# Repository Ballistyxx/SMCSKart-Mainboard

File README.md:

# SMCSKart Mainboard

Custom PCB integrating every system in the SMCS Robotics 8th period go-kart. The board acts as the central hub between a Raspberry Pi 4, a Teensy 4.1, all motor controller I/O, sensors, and peripherals.

<div style="display: flex; justify-content: space-between;">

</div>

---

## Components

| Component | Description |
|-----------|-------------|
| Raspberry Pi 4 | Main compute; connected via 40-pin header |
| Teensy 4.1 | Real-time microcontroller with onboard Ethernet |
| NEO-M9N | GPS module (connected to Pi I2C + PPS to Teensy) |
| MPU6050 | 6-axis accelerometer/gyroscope (connected to Pi I2C) |
| MCP4725 | 12-bit DAC for throttle signal generation (connected to Teensy I2C) |
| MCP2562-E/P | CAN bus transceiver |
| IRLZ44N | Logic-level N-channel MOSFETs for all toggle/switch outputs (with pulldown resistors) |
| ND721000 | FarDriver BLDC/PMSM speed controller (RS232 interface) |

---

## Power Rails

The board supplies three voltage rails available on the extra power port:

| Rail | Voltage |
|------|---------|
| 3V3 | 3.3 V |
| 5V | 5 V |
| 24V | 24 V (also used for LED strip) |

---

## Teensy 4.1 Pin Assignments

### Serial / UART

| Pin(s) | Interface | Connected To | Notes |
|--------|-----------|--------------|-------|
| 0, 1 | Serial1 (TX, RX) | ND721000 ESC | RS232 level — programming/telemetry port on ESC |
| 7, 8 | Serial2 (TX, RX) | Raspberry Pi 4 | UART bridge between Teensy and Pi |
| 14, 15 | Serial3 (TX, RX) | Transceiver module | RF/wireless transceiver comms |
| 34, 35 | Serial8 (TX, RX) | FPV camera | UART control for FPV camera |

### I2C

| Pin(s) | Bus | Connected To |
|--------|-----|--------------|
| 18, 19 | SDA, SCL | MCP4725 DAC (throttle control) |

### CAN Bus

| Pin(s) | Signal | Notes |
|--------|--------|-------|
| 30, 31 | CRX, CTX | Via MCP2562-E/P transceiver; 120 Ω termination required at each end |

### Digital I/O — ESC Control & Sensors

All toggle output pins drive an IRLZ44N MOSFET with a pulldown resistor, providing an active-low ground signal to the ESC connector.

| Pin | Function | ESC Signal | Direction |
|-----|----------|------------|-----------|
| 2 | Hall Pulses input | Hall Pulses (ESC pin 18) | Input from ESC |
| 3 | Reverse toggle | REV (ESC pin 8) | Output to ESC |
| 4 | Brake toggle | Low Brake (ESC pin 21) | Output to ESC |
| 5 | High speed toggle | High Speed (ESC pin 3) | Output to ESC |
| 6 | Low speed toggle | Low Speed (ESC pin 2) | Output to ESC |
| 9 | Cruise control | Cruise/Boost connector | Output to ESC |
| 10 | PPS | NEO-M9N GPS pulse-per-second | Input from GPS |
| 32 | Contactor toggle | Main contactor relay | Output |

### PWM — LED Strip (24 V)

| Pin | Channel |
|-----|---------|
| 37 | Red |
| 36 | Green |
| 33 | Blue |

### Auxiliary (EX1–EX5)

| Pin | Label |
|-----|-------|
| 25 | EX1 |
| 26 | EX2 |
| 27 | EX3 |
| 28 | EX4 |
| 29 | EX5 |

---

## Raspberry Pi 4 I2C Bus

| Device | Address | Function |
|--------|---------|----------|
| NEO-M9N | — | GPS module |
| MPU6050 | 0x68 | Accelerometer / Gyroscope |

---

## ND721000 ESC Interface

The Teensy communicates with the ND721000 over **Serial1 (pins 0/1) at RS232 levels** (programming/telemetry port). In addition, discrete signals are routed between the board and the ESC's connector harness.

### ESC Connector Pin Reference

| ESC Pin | Color | Signal | Direction | Teensy Pin | Notes |
|---------|-------|--------|-----------|------------|-------|
| 1 | Yellow | Hall A | → ESC | — | Motor hall sensor A |
| 2 | Blue-White | Low Speed | ← Teensy | 6 | Ground to activate low speed profile |
| 3 | Yellow-White | High Speed | ← Teensy | 5 | Ground to activate high speed profile |
| 4 | Red | HALL+ | — | — | ~14 V supply to hall sensors / encoder |
| 5 | Brown-Yellow | CAN L | ↔ | — | CAN bus low (optional; 120 Ω termination required) |
| 6 | Black | GND (Hall) | — | — | Hall sensor ground |
| 7 | Black | B− / GND | — | — | Battery negative / signal ground |
| 8 | Brown-White | REV | ← Teensy | 3 | Ground to request reverse direction |
| 9 | Purple | Speedometer signal | → | — | Analog speed output for speedometer gauge |
| 10 | Orange | Key | — | — | Main power-on input (connect to key switch via 5A fuse) |
| 11 | Gray | High Brake | ← Teensy | 4 | Active-high (12 V) brake input |
| 12 | Green | Hall B | → ESC | — | Motor hall sensor B |
| 13 | Light-Blue | SPD (digital speed pulse) | → | — | Square-wave RPM output for digital speedo / ECU |
| 14 | Black-White | FW (anti-theft) | ← | — | Ground to activate anti-theft lockout (error code 6) |
| 15 | Red-Yellow | CAN H | ↔ | — | CAN bus high (optional; 120 Ω termination required) |
| 16 | Black | GND (serial/switch) | — | — | Signal ground for serial and switch circuits |
| 17 | White | Hall P (encoder index) | → ESC | — | Once-per-revolution encoder reference pulse |
| 18 | Brown | Hall Pulses signal | → Teensy | 2 | Speed pulse output used as tachometer reference |
| 19 | Brown-Red | Lock Phase | — | — | Anti-theft motor phase lock wire |
| 20 | Orange | Key (anti-theft) | — | — | Secondary key input for anti-theft subsystem |
| 21 | Yellow-Green | Low Brake | ← Teensy | 4 | Active-low brake input; ground to signal braking |
| 22 | Blue | Hall C | → ESC | — | Motor hall sensor C |
| 23 | Brown-Blue | TxD (serial) | → Teensy | 0 (RX) | ESC serial transmit → Teensy Serial1 RX |
| 24 | White | Motor Temp | → ESC | — | Motor temperature sensor (PTC/NTC/KTY) |
| 25 | — | — | — | — | — |
| 26 | Black | GND (throttle/brake) | — | — | Shared signal ground for throttle and brake circuits |
| 27 | Green-White | TPS (throttle) | ← DAC | — | Throttle position signal (0.5–4.3 V); driven by MCP4725 |
| 28 | Red-White | ACC+ (5 V) | → throttle sensor | — | 5 V regulated supply for throttle sensor |
| 29 | Brown-Green | V+ (serial power) | → adapter | — | 5 V supply for USB-TTL programming adapter |
| 30 | Pink | B+ (anti-theft) | — | — | Always-live battery positive for anti-theft device |
| 31 | Brown-Red | RxD (serial) | ← Teensy | 1 (TX) | ESC serial receive ← Teensy Serial1 TX |

> **Note:** High Brake (pin 11) is active-high (12 V) while Low Brake (pin 21) is active-low (GND). Both can signal braking; the board uses pin 21 via MOSFET toggle (Teensy pin 4).
> **Note:** Medium speed mode is the ESC default when neither High Speed nor Low Speed is grounded.

---

## External Connectors / Ports

| Port | Description |
|------|-------------|
| 40-pin header | Raspberry Pi 4 HAT connector |
| USB-A | HID peripheral (keyboard, gamepad, etc.) |
| Ethernet | Networking (Teensy 4.1 native Ethernet) |
| CAN × 3 | CANBUS + I2C interface ports |
| Contactor | Trigger port for main contactor relay (Teensy pin 32) |
| FPV camera | UART port (Teensy Serial8, pins 34/35) |
| Transceiver | RF transceiver UART port (Teensy Serial3, pins 14/15) |
| Power port | Extra 3V3 / 5V / 24V supply breakout |
| LED strip | 24 V RGB PWM output (pins 37, 36, 33) |

For images of each port's annotated pinout, see [./docs/PINOUTS.md](./docs/PINOUTS.md)

Made by Eli Ferrara, SMCS Class of 2026
MIT License

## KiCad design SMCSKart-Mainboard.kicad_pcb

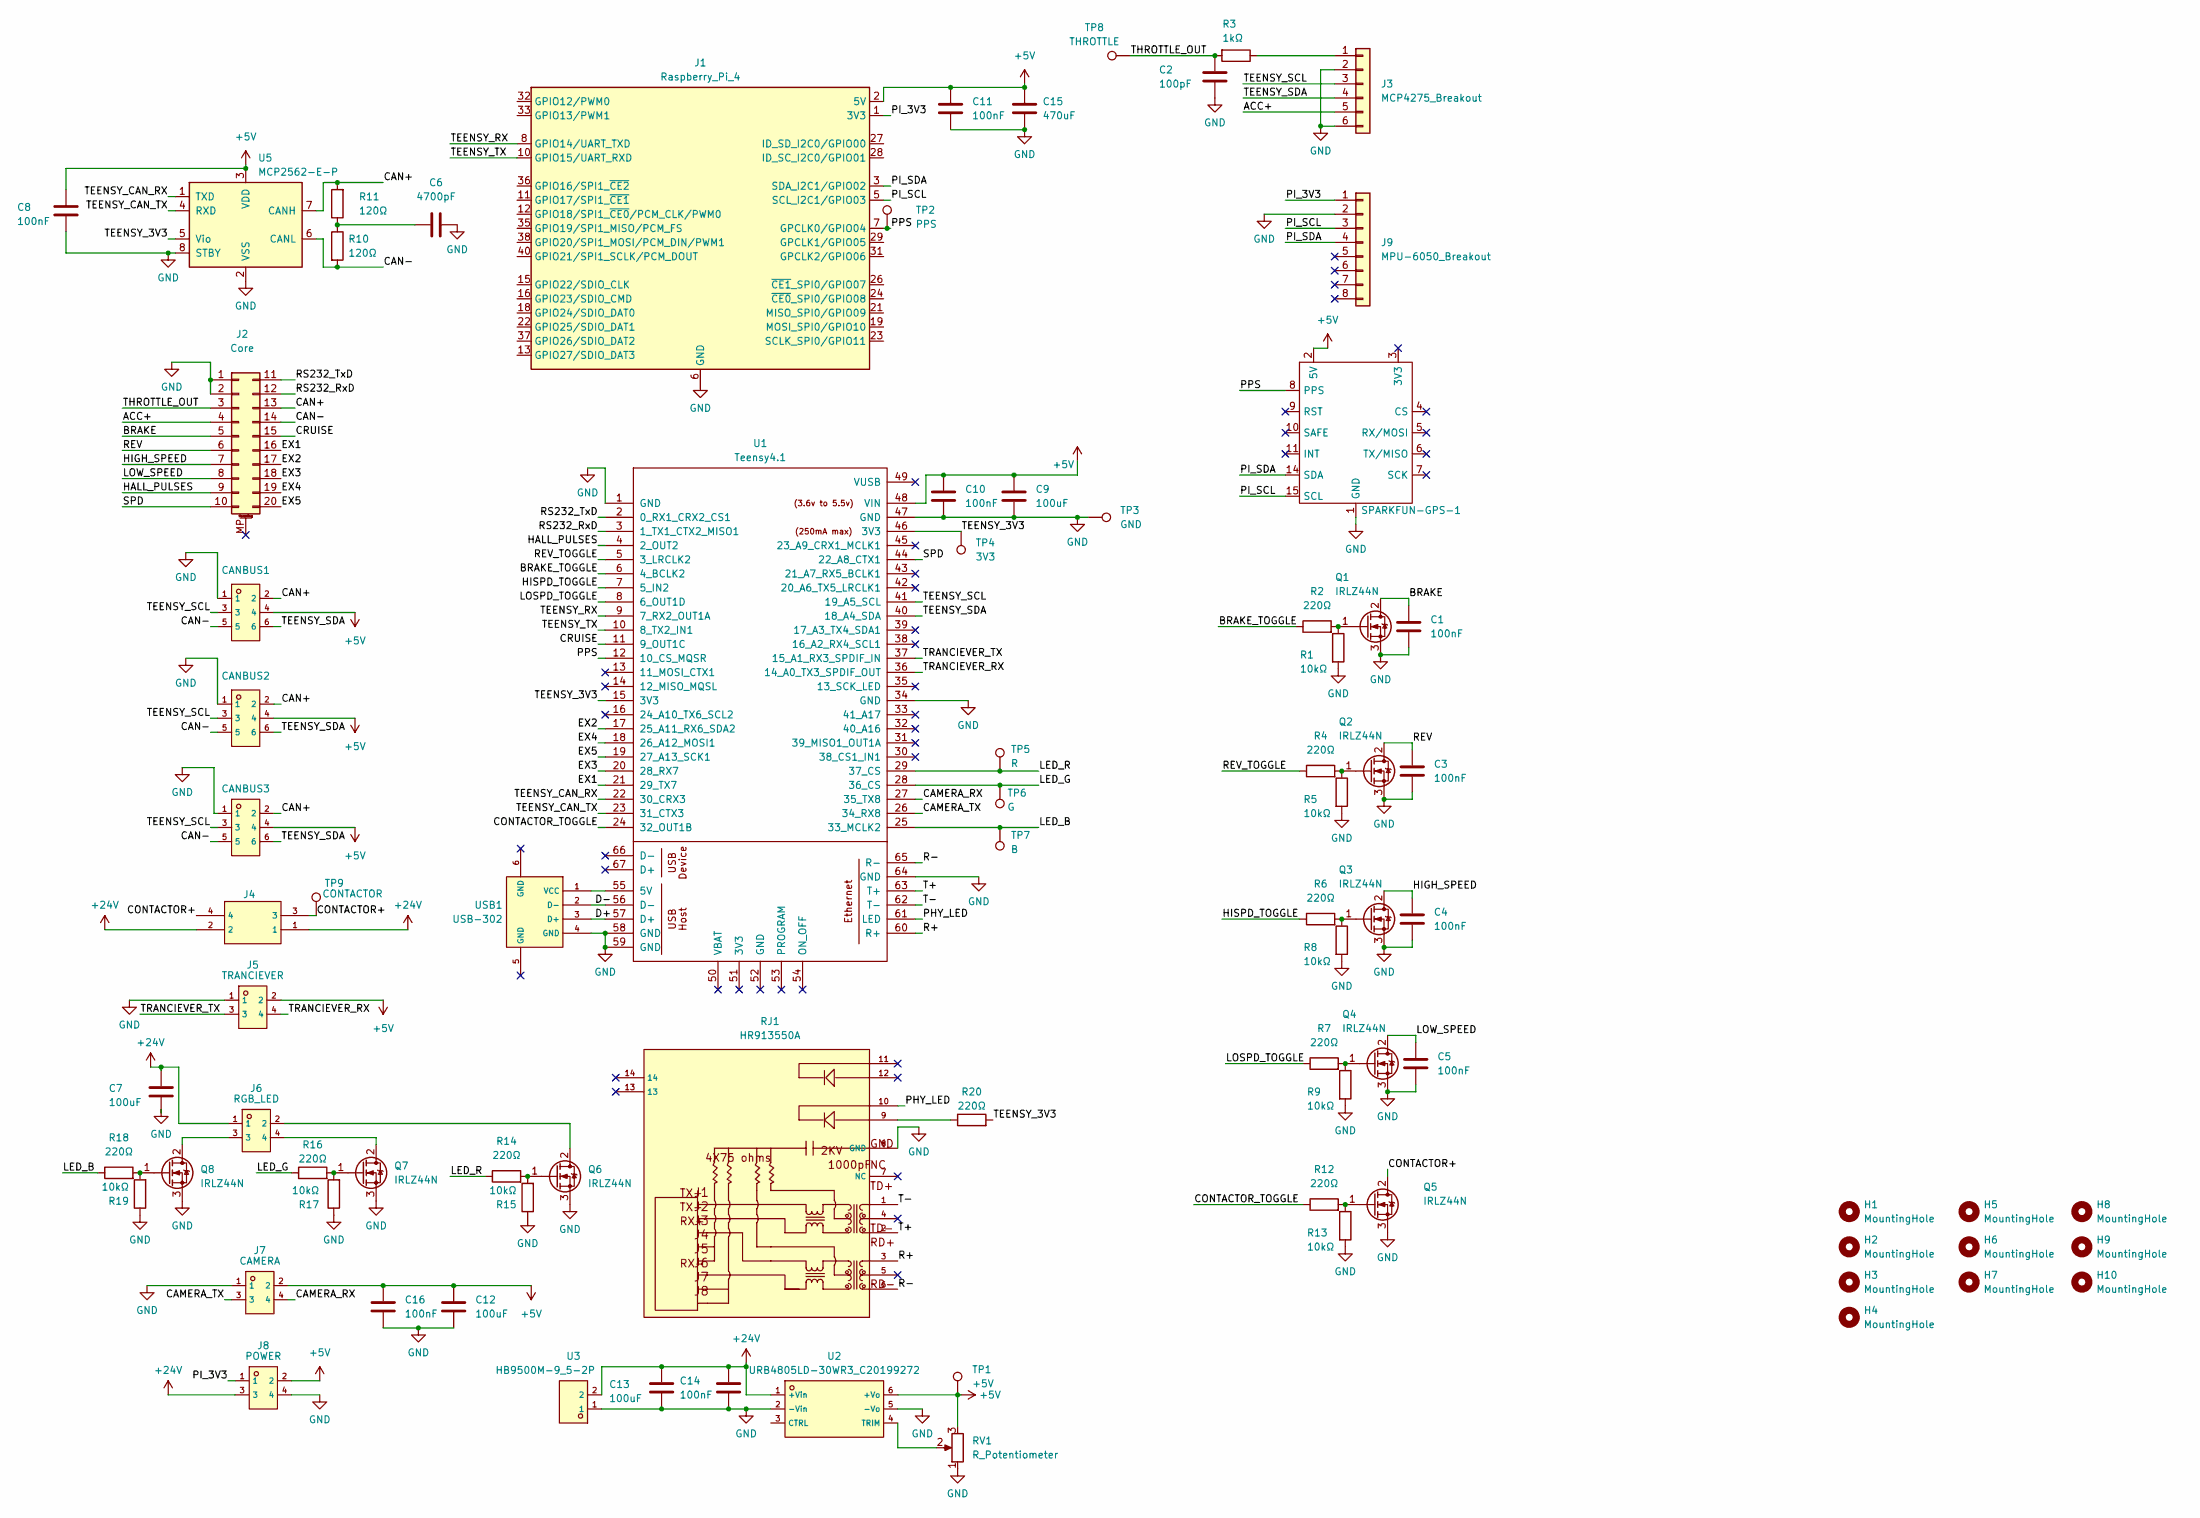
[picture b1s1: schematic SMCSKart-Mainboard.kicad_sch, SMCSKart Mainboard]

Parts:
C1, C3, C4, C5, C8, C10, C11, C14, C16: 100nF; C_Disc_D4.3mm_W1.9mm_P5.00mm
C2: 100pF; C_Disc_D6.0mm_W2.5mm_P5.00mm
C6: 4700pF; C_Disc_D5.1mm_W3.2mm_P5.00mm
C7, C9, C12, C13: 100uF; C_Radial_D8.0mm_H7.0mm_P3.50mm
C15: 470uF; C_Radial_D6.3mm_H7.0mm_P2.50mm
CANBUS1, CANBUS2, CANBUS3: ZX-MX3_0-2-3PWZ; Molex_Micro-Fit_3.0_43045-0600_2x03_P3.00mm_Horizontal; LCSC C7541602
H1, H2, H3, H4: MountingHole; MountingHole_2.7mm_M2.5_DIN965_Pad
H5, H6, H7: MountingHole; MountingHole_3.2mm_M3_DIN965_Pad
H8, H9: MountingHole; MountingHole_3.2mm_M3
H10: MountingHole; MountingHole_2.2mm_M2_DIN965
J1: Raspberry_Pi_4; PinSocket_2x20_P2.54mm_Vertical
J2: Core; CONN-TH_20P-P3.00_HC-MX3.0-2X10AW
J3: MCP4275_Breakout; PinHeader_1x06_P2.54mm_Vertical
J4: 0430450400; CONN-TH_0430450400; LCSC C122413
J5: TRANCIEVER; CONN-TH_4P-P3.00_HC-MX3.0-2X2A; LCSC C7541613
J6: RGB_LED; CONN-TH_4P-P3.00_HC-MX3.0-2X2A; LCSC C7541613
J7: CAMERA; CONN-TH_4P-P3.00_HC-MX3.0-2X2A; LCSC C7541613
J8: POWER; CONN-TH_4P-P3.00_HC-MX3.0-2X2A; LCSC C7541613
J9: MPU-6050_Breakout; PinHeader_1x08_P2.54mm_Vertical
Q1, Q2, Q3, Q4, Q5, Q6, Q7, Q8: IRLZ44N; TO-220-3_Vertical
R1, R5, R8, R9, R13, R15, R17, R19: 10kΩ; R_Axial_DIN0207_L6.3mm_D2.5mm_P7.62mm_Horizontal
R2, R4, R6, R7, R12, R14, R16, R18, R20: 220Ω; R_Axial_DIN0207_L6.3mm_D2.5mm_P7.62mm_Horizontal
R3: 1kΩ; R_Axial_DIN0207_L6.3mm_D2.5mm_P7.62mm_Horizontal
R10, R11: 120Ω; R_Axial_DIN0207_L6.3mm_D2.5mm_P7.62mm_Horizontal
RJ1: HR913550A; RJ45-TH_HR913550A; LCSC C163507
RV1: R_Potentiometer; Potentiometer_Bourns_3266Y_Vertical
SPARKFUN-GPS-1: Sparkfun-NEO-M9N-Breakout-Board
TP1: +5V; TestPoint_Pad_D4.0mm
TP2: PPS; TestPoint_Pad_D4.0mm
TP3: GND; TestPoint_Pad_D4.0mm
TP4: 3V3; TestPoint_Pad_D4.0mm
TP5: R; TestPoint_Pad_D4.0mm
TP6: G; TestPoint_Pad_D4.0mm
TP7: B; TestPoint_Pad_D4.0mm
TP8: THROTTLE; TestPoint_Pad_D4.0mm
TP9: CONTACTOR; TestPoint_Pad_D4.0mm
U1: Teensy4.1; Teensy41
U2: URB4805LD-30WR3_C20199272; PWRM-TH_TURBXXXXLD-30WR3; LCSC C20199272
U3: HB9500M-9_5-2P; CONN-TH_HB9500M-9.5-2P; LCSC C601239
U5: MCP2562-E-P; DIP-8_W7.62mm
USB1: USB-302; USB-A-TH_USB-302-T; LCSC C112456

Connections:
+5V: C8.1, C9.1, C10.1, C11.1, C12.1, C15.1, C16.1, CANBUS1.4, CANBUS2.4, CANBUS3.4, J1.2 (5V), J1.4 (5V), J5.2, J7.2, J8.2, RV1.3, SPARKFUN-GPS-1.2 (5V), TP1.1, U1.48 (VIN), U2.6 (+Vo), U5.3 (VDD)
+24V: C7.1, C13.1, C14.1, J4.1, J4.2, J6.1, J8.3, U2.1 (+Vin), U3.2
/ACC+: J2.4, J3.5
/BRAKE: C1.1, J2.5, Q1.2 (D)
/BRAKE_TOGGLE: R2.1, U1.6 (4_BCLK2)
/CAMERA_RX: J7.4, U1.27 (35_TX8)
/CAMERA_TX: J7.3, U1.26 (34_RX8)
/CAN+: CANBUS1.2, CANBUS2.2, CANBUS3.2, J2.13, R11.2, U5.7 (CANH)
/CAN-: CANBUS1.5, CANBUS2.5, CANBUS3.5, J2.14, R10.2, U5.6 (CANL)
/CONTACTOR+: J4.3, J4.4, Q5.2 (D), TP9.1
/CONTACTOR_TOGGLE: R12.1, U1.24 (32_OUT1B)
/CRUISE: J2.15, U1.11 (9_OUT1C)
/D+: U1.57 (D+), USB1.3 (D+)
/D-: U1.56 (D-), USB1.2 (D-)
/EX1: J2.16, U1.21 (29_TX7)
/EX2: J2.17, U1.17 (25_A11_RX6_SDA2)
/EX3: J2.18, U1.20 (28_RX7)
/EX4: J2.19, U1.18 (26_A12_MOSI1)
/EX5: J2.20, U1.19 (27_A13_SCK1)
/HALL_PULSES: J2.9, U1.4 (2_OUT2)
/HIGH_SPEED: C4.1, J2.7, Q3.2 (D)
/HISPD_TOGGLE: R6.1, U1.7 (5_IN2)
/LED_B: R18.1, TP7.1, U1.25 (33_MCLK2)
/LED_G: R16.1, TP6.1, U1.28 (36_CS)
/LED_R: R14.1, TP5.1, U1.29 (37_CS)
/LOSPD_TOGGLE: R7.1, U1.8 (6_OUT1D)
/LOW_SPEED: C5.1, J2.8, Q4.2 (D)
/PHY_LED: RJ1.10, U1.61 (LED)
/PI_3V3: J1.1 (3V3), J1.17 (3V3), J8.1, J9.1
/PI_SCL: J1.5 (SCL_I2C1/GPIO03), J9.3, SPARKFUN-GPS-1.15 (SCL)
/PI_SDA: J1.3 (SDA_I2C1/GPIO02), J9.4, SPARKFUN-GPS-1.14 (SDA)
/PPS: J1.7 (GPCLK0/GPIO04), SPARKFUN-GPS-1.8 (PPS), TP2.1, U1.12 (10_CS_MQSR)
/R+: RJ1.3, U1.60 (R+)
/R-: RJ1.6, U1.65 (R-)
/REV: C3.1, J2.6, Q2.2 (D)
/REV_TOGGLE: R4.1, U1.5 (3_LRCLK2)
/RS232_RxD: J2.12, U1.3 (1_TX1_CTX2_MISO1)
/RS232_TxD: J2.11, U1.2 (0_RX1_CRX2_CS1)
/SPD: J2.10, U1.44 (22_A8_CTX1)
/T+: RJ1.2, U1.63 (T+)
/T-: RJ1.1, U1.62 (T-)
/TEENSY_3V3: R20.2, TP4.1, U1.15 (3V3), U1.46 (3V3), U5.5 (Vio)
/TEENSY_CAN_RX: U1.22 (30_CRX3), U5.1 (TXD)
/TEENSY_CAN_TX: U1.23 (31_CTX3), U5.4 (RXD)
/TEENSY_RX: J1.8 (GPIO14/UART_TXD), U1.9 (7_RX2_OUT1A)
/TEENSY_SCL: CANBUS1.3, CANBUS2.3, CANBUS3.3, J3.3, U1.41 (19_A5_SCL)
/TEENSY_SDA: CANBUS1.6, CANBUS2.6, CANBUS3.6, J3.4, U1.40 (18_A4_SDA)
/TEENSY_TX: J1.10 (GPIO15/UART_RXD), U1.10 (8_TX2_IN1)
/THROTTLE_OUT: C2.1, J2.3, R3.2, TP8.1
/TRANCIEVER_RX: J5.4, U1.36 (14_A0_TX3_SPDIF_OUT)
/TRANCIEVER_TX: J5.3, U1.37 (15_A1_RX3_SPDIF_IN)
GND: C1.2, C2.2, C3.2, C4.2, C5.2, C6.1, C7.2, C8.2, C9.2, C10.2, C11.2, C12.2, C13.2, C14.2, C15.2, C16.2, CANBUS1.1, CANBUS2.1, CANBUS3.1, J1.6 (GND), J1.9 (GND), J1.14 (GND), J1.20 (GND), J1.25 (GND), J1.30 (GND), J1.34 (GND), J1.39 (GND), J2.1, J2.2, J3.2, J3.6, J5.1, J7.1, J8.4, J9.2, Q1.3 (S), Q2.3 (S), Q3.3 (S), Q4.3 (S), Q5.3 (S), Q6.3 (S), Q7.3 (S), Q8.3 (S), R1.2, R5.2, R8.2, R9.2, R13.2, R15.1, R17.1, R19.1, RJ1.8 (GND), RV1.1, SPARKFUN-GPS-1.1 (GND), TP3.1, U1.1 (GND), U1.34 (GND), U1.47 (GND), U1.58 (GND), U1.59 (GND), U1.64 (GND), U2.2 (-Vin), U2.5 (-Vo), U3.1, U5.2 (VSS), U5.8 (STBY), USB1.4 (GND)
unnamed: C6.2, R10.1, R11.1
unnamed: J3.1, R3.1
unnamed: Q1.1 (G), R1.1, R2.2
unnamed: Q2.1 (G), R4.2, R5.1
unnamed: Q3.1 (G), R6.2, R8.1
unnamed: Q4.1 (G), R7.2, R9.1
unnamed: Q5.1 (G), R12.2, R13.1
unnamed: J6.2, Q6.2 (D)
unnamed: Q6.1 (G), R14.2, R15.2
unnamed: J6.4, Q7.2 (D)
unnamed: Q7.1 (G), R16.2, R17.2
unnamed: J6.3, Q8.2 (D)
unnamed: Q8.1 (G), R18.2, R19.2
unnamed: R20.1, RJ1.9
unnamed: U1.55 (5V), USB1.1 (VCC)
unnamed: RV1.2, U2.4 (TRIM)

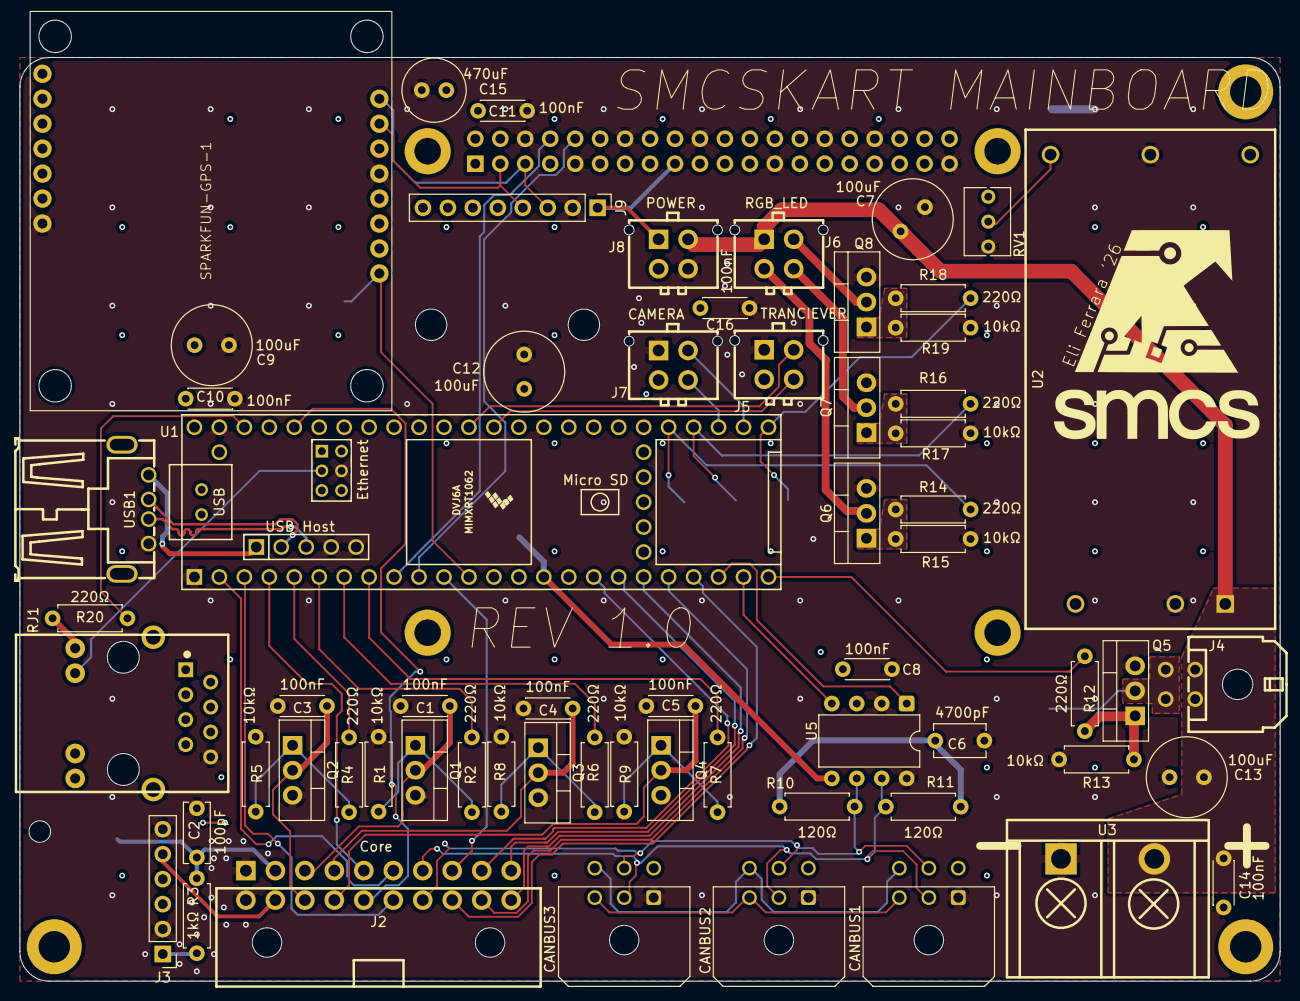
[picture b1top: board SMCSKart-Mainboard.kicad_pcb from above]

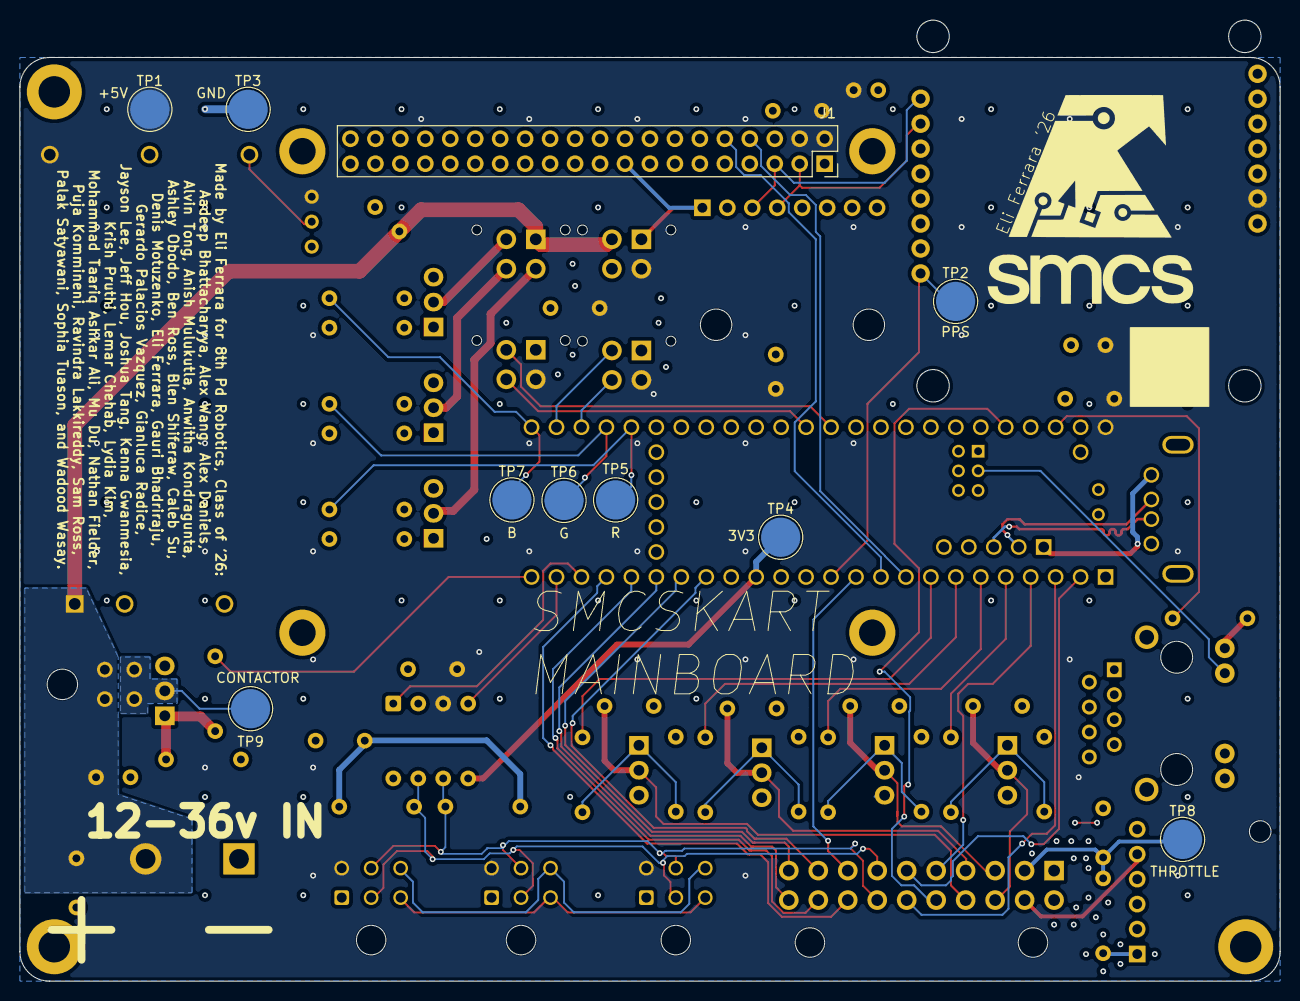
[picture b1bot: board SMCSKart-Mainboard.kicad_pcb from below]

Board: 4 copper layers, 128.2 x 97.8 mm, 83 parts (10 on the bottom side), 68 nets.

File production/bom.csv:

Designator,Footprint,Quantity,Value,LCSC Part #
"C1, C10, C11, C14, C16, C3, C4, C5, C8",C_Disc_D4.3mm_W1.9mm_P5.00mm,9,100nF,
"C12, C13, C7, C9",C_Radial_D8.0mm_H7.0mm_P3.50mm,4,100uF,
C15,C_Radial_D6.3mm_H7.0mm_P2.50mm,1,470uF,
C2,C_Disc_D6.0mm_W2.5mm_P5.00mm,1,100pF,
C6,C_Disc_D5.1mm_W3.2mm_P5.00mm,1,4700pF,
"CANBUS1, CANBUS2, CANBUS3",Molex_Micro-Fit_3.0_43045-0600_2x03_P3.00mm_Horizontal,3,ZX-MX3_0-2-3PWZ,C7541602
J1,PinSocket_2x20_P2.54mm_Vertical,1,Raspberry_Pi_4,
J2,CONN-TH_20P-P3.00_HC-MX3.0-2X10AW,1,Core,
J3,PinHeader_1x06_P2.54mm_Vertical,1,MCP4275_Breakout,
J4,CONN-TH_0430450400,1,0430450400,C122413
J5,CONN-TH_4P-P3.00_HC-MX3.0-2X2A,1,TRANCIEVER,C7541613
J6,CONN-TH_4P-P3.00_HC-MX3.0-2X2A,1,RGB_LED,C7541613
J7,CONN-TH_4P-P3.00_HC-MX3.0-2X2A,1,CAMERA,C7541613
J8,CONN-TH_4P-P3.00_HC-MX3.0-2X2A,1,POWER,C7541613
J9,PinHeader_1x08_P2.54mm_Vertical,1,MPU-6050_Breakout,
"Q1, Q2, Q3, Q4, Q5, Q6, Q7, Q8",TO-220-3_Vertical,8,IRLZ44N,
"R1, R13, R15, R17, R19, R5, R8, R9",R_Axial_DIN0207_L6.3mm_D2.5mm_P7.62mm_Horizontal,8,10kΩ,
"R10, R11",R_Axial_DIN0207_L6.3mm_D2.5mm_P7.62mm_Horizontal,2,120Ω,
"R12, R14, R16, R18, R2, R20, R4, R6, R7",R_Axial_DIN0207_L6.3mm_D2.5mm_P7.62mm_Horizontal,9,220Ω,
R3,R_Axial_DIN0207_L6.3mm_D2.5mm_P7.62mm_Horizontal,1,1kΩ,
RJ1,RJ45-TH_HR913550A,1,HR913550A,C163507
RV1,Potentiometer_Bourns_3266Y_Vertical,1,R_Potentiometer,
SPARKFUN-GPS-1,Sparkfun-NEO-M9N-Breakout-Board,1,~,
TP1,TestPoint_Pad_D4.0mm,1,+5V,
TP2,TestPoint_Pad_D4.0mm,1,PPS,
TP3,TestPoint_Pad_D4.0mm,1,GND,
TP4,TestPoint_Pad_D4.0mm,1,3V3,
TP5,TestPoint_Pad_D4.0mm,1,R,
TP6,TestPoint_Pad_D4.0mm,1,G,
TP7,TestPoint_Pad_D4.0mm,1,B,
TP8,TestPoint_Pad_D4.0mm,1,THROTTLE,
TP9,TestPoint_Pad_D4.0mm,1,CONTACTOR,
U1,Teensy41,1,Teensy4.1,
U2,PWRM-TH_TURBXXXXLD-30WR3,1,URB4805LD-30WR3_C20199272,C20199272
U3,CONN-TH_HB9500M-9.5-2P,1,HB9500M-9_5-2P,C601239
U5,DIP-8_W7.62mm,1,MCP2562-E-P,
USB1,USB-A-TH_USB-302-T,1,USB-302,C112456

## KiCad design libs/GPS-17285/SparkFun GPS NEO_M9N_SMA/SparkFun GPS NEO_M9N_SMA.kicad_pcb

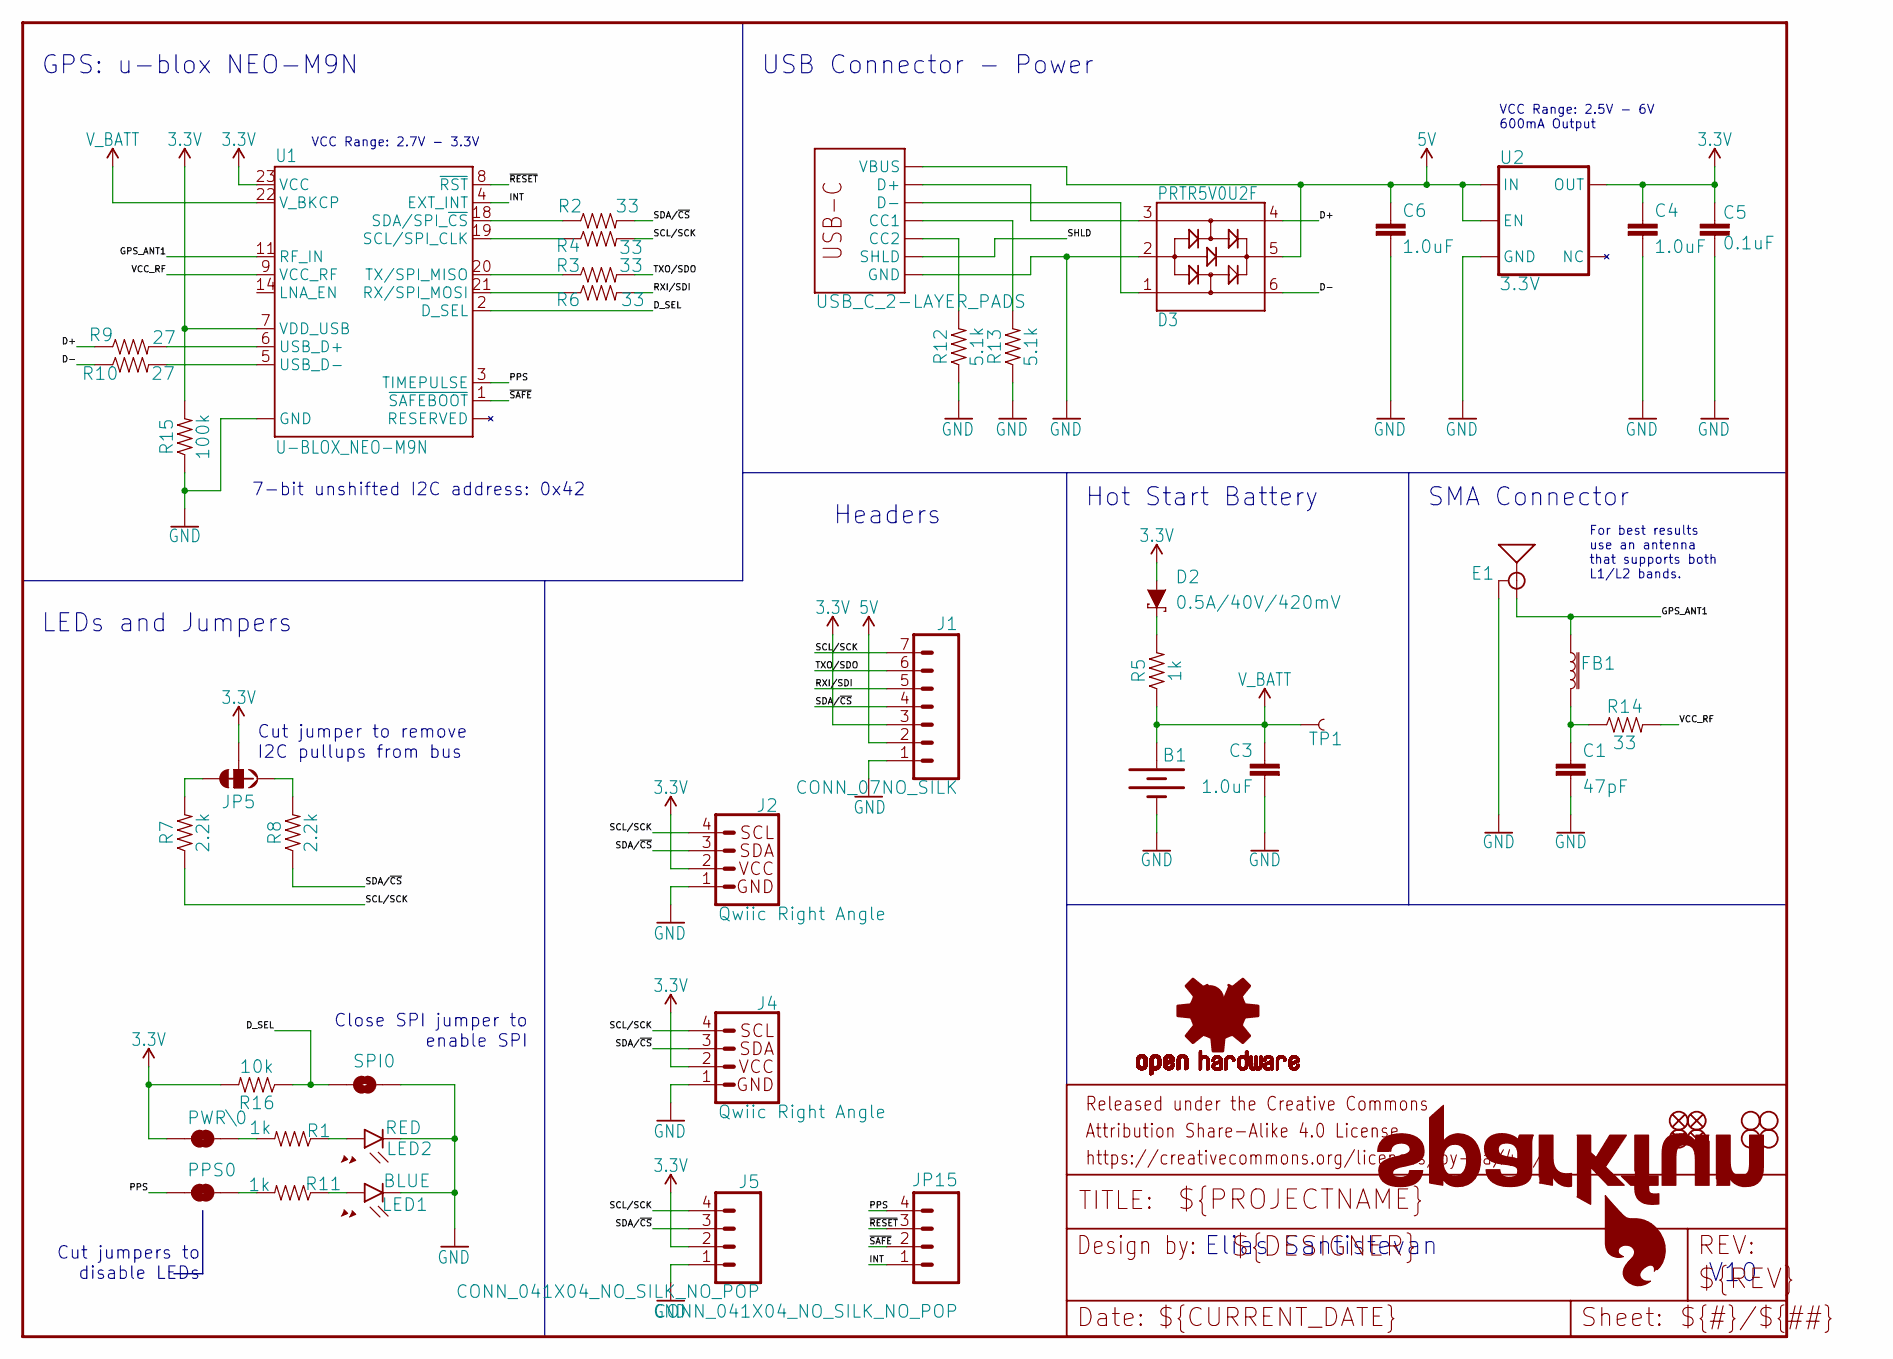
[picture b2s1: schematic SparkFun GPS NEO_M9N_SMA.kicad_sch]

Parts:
B1: 6.8MM_COIN_CELL; ML414H_IV01E
C1: 47pF; 0402
C3, C4, C6: 1.0uF; 0603
C5: 0.1uF; 0603
D2: 0.5A/40V/420mV; SOD-323
D3: PRTR5V0U2F; SOT886
E1: ANTENNA-GROUNDEDEDGE_SMA_SMD; SMA-EDGE-SMD
FB1: FERRITE_BEAD-120_OHM-0402; 0402
FRAME1: FRAME-LETTER; CREATIVE_COMMONS
J1: CONN_07NO_SILK; 1X07_NO_SILK
J2, J4: Qwiic Right Angle; JST04_1MM_RA
J3: USB_C_2-LAYER_PADS; USB-C-16P-2LAYER-PADS
J5: CONN_041X04_NO_SILK_NO_POP; 1X04_NO_SILK
JP1, JP31, JP91, JP101: STAND-OFF
JP5: JUMPER-SMT_3_2-NC_TRACE_SILK; SMT-JUMPER_3_2-NC_TRACE_SILK
JP15: CONN_041X04_NO_SILK_NO_POP; 1X04_NO_SILK
JP21, JP61, JP71, JP81: FIDUCIALUFIDUCIAL; MICRO-FIDUCIAL
LED1: BLUE; LED-0603
LED2: RED; LED-0603
LOGO1: OSHW-LOGOMINI; OSHW-LOGO-MINI
LOGO2: SFE_LOGO_NAME_FLAME.1_INCH; SFE_LOGO_NAME_FLAME_.1
PPS0: JUMPER-SMT_2_NC_TRACE_SILK; SMT-JUMPER_2_NC_TRACE_SILK
PWR\0: JUMPER-SMT_2_NC_TRACE_SILK; SMT-JUMPER_2_NC_TRACE_SILK
R1, R5, R11: 1k; 0603
R2, R3, R4, R6: 33; 0603
R7, R8: 2.2k; 0603
R9, R10: 27; 0603
R12, R13: 5.1k; 0603
R14: 33; 0402
R15: 100k; 0603
R16: 10k; 0402
SPI0: JUMPER-SMT_2_NO_SILK; SMT-JUMPER_2_NO_SILK
TP1: TEST-POINT3X4; PAD.03X.04
U1: U-BLOX_NEO-M9N; NEO-M9N_M8T_M8U
U2: 3.3V; SOT23-5

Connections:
3.3V: C4.1, C5.2, D2.A, J1.3, J2.2, J4.2, J5.2, JP5.2, PWR\0.2, R15.2, R16.2, U1.7 (VDD_USB), U1.23 (VCC), U2.5 (OUT)
5V: C6.1, D3.5, J1.2, J3.VBUS1 (VBUS), J3.VBUS2 (VBUS), U2.1 (IN), U2.3 (EN)
D+: D3.4, R9.1
D-: D3.6, R10.1
D_SEL: R16.1, SPI0.2, U1.2 (D_SEL)
GND: B1.-, C1.2, C3.2, C4.2, C5.1, C6.2, D3.2, E1.GND@0 (GND), E1.GND@1 (GND), J1.1, J2.1, J3.GND, J3.GND2 (GND), J4.1, J5.1, LED1.C, LED2.C, R12.1, R13.1, R15.1, SPI0.1, U1.10 (GND), U1.12 (GND), U1.13 (GND), U1.24 (GND), U2.2 (GND)
GPS_ANT1: E1.SIG (SIGNAL), FB1.1, U1.11 (RF_IN)
INT: JP15.1, U1.4 (EXT_INT)
unnamed: PWR\0.1, R1.2
unnamed: LED1.A, R11.1
unnamed: C1.1, FB1.2, R14.1
unnamed: PPS0.1, R11.2
unnamed: JP5.1, R8.2
unnamed: D2.C, R5.2
unnamed: J3.B5 (CC2), R12.2
unnamed: JP5.3, R7.2
unnamed: J3.A5 (CC1), R13.2
unnamed: LED2.A, R1.1
unnamed: R9.2, U1.6 (USB_D+)
unnamed: R10.2, U1.5 (USB_D-)
PPS: JP15.4, PPS0.2, U1.3 (TIMEPULSE)
RXI/SDI: J1.5, R6.2
RXLV: R6.1, U1.21 (RX/SPI_MOSI)
SCL/SCK: J1.7, J2.4, J4.4, J5.4, R4.2, R7.1
SCL_LV: R4.1, U1.19 (SCL/SPI_CLK)
SDA/~CS: J1.4, J2.3, J4.3, J5.3, R2.2, R8.1
SDA_LV: R2.1, U1.18 (SDA/SPI_~CS)
SHLD: J3.SHLD1 (SHLD), J3.SHLD2 (SHLD), J3.SHLD3 (SHLD), J3.SHLD4 (SHLD)
TXLV: R3.1, U1.20 (TX/SPI_MISO)
TXO/SDO: J1.6, R3.2
USB_D+: D3.3, J3.A6 (D+), J3.B6 (D+)
USB_D-: D3.1, J3.A7 (D-), J3.B7 (D-)
VCC_RF: R14.2, U1.9 (VCC_RF)
V_BATT: B1.+, C3.1, R5.1, TP1.P$1, U1.22 (V_BKCP)
~RESET: JP15.3, U1.8 (~RST)
~SAFE: JP15.2, U1.1 (~SAFEBOOT)

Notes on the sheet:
USB Connector - Power
Cut jumper to remove I2C pullups from bus
7-bit unshifted I2C address: 0x42
VCC Range: 2.5V - 6V 600mA Output
Hot Start Battery
GPS: u-blox NEO-M9N
VCC Range: 2.7V - 3.3V
LEDs and Jumpers
Close SPI jumper to enable SPI
For best results use an antenna that supports both L1/L2 bands.
Elias Santistevan
Headers
V10
SMA Connector
Cut jumpers to disable LEDs

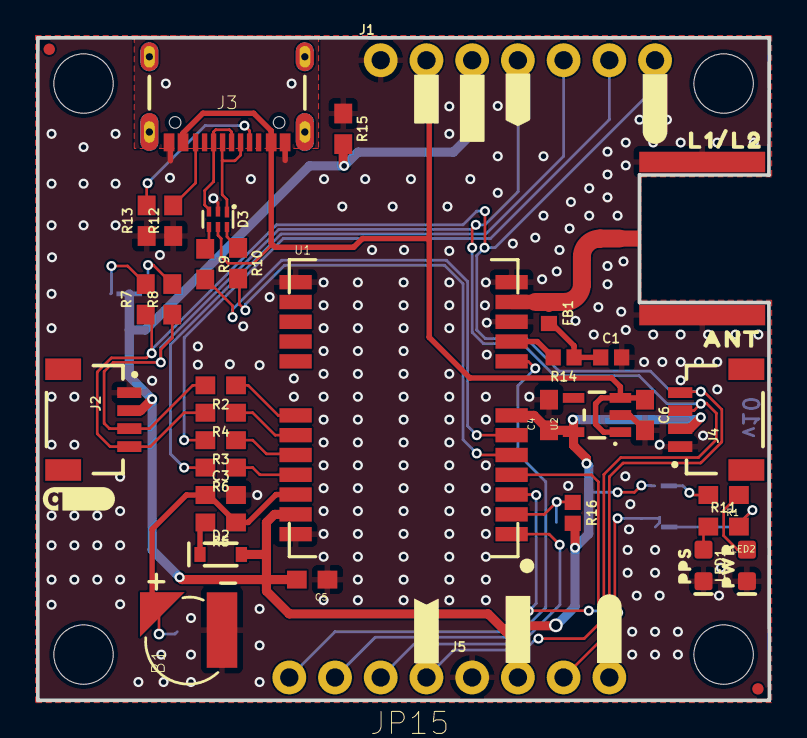
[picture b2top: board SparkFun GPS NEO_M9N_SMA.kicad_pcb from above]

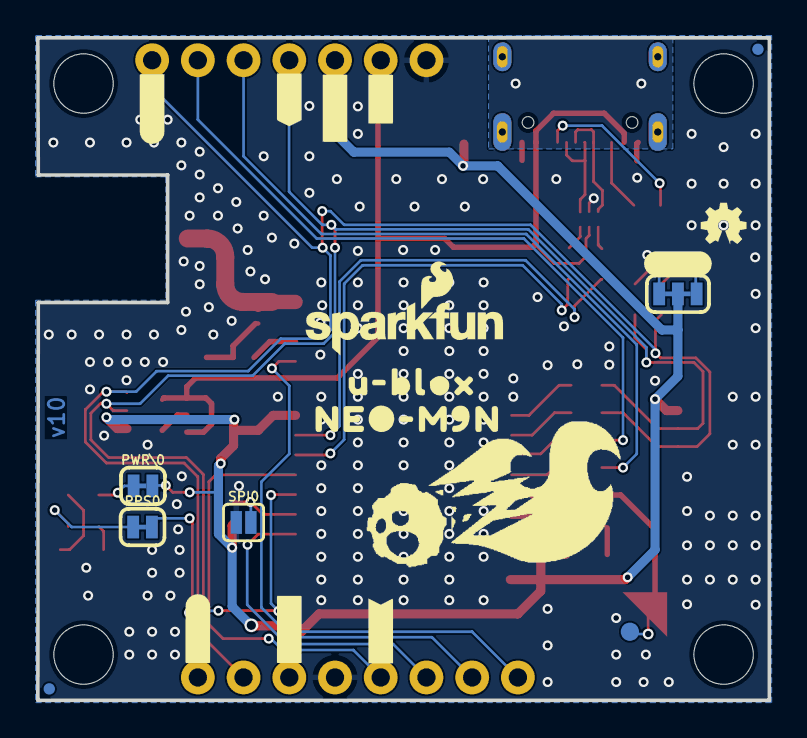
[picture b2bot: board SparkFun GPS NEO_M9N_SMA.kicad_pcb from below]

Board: 2 copper layers, 40.6 x 36.8 mm, 94 parts (31 on the bottom side), 36 nets.

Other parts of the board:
U$1: ##CS##9
U$2: U#BLOX19
U$3: ##SAFE##15
U$4, U$5, U$39, U$40: #3V3#6
U$6, U$42: #5V#1
U$7, U$8, U$38, U$41: #GND#0
U$9: #INT#16
U$10: PPS7
U$11, U$32: #PPS#13
U$12: #SPI#22
U$13: PWR6
U$14: QWIIC_4MM
U$15: #RX#SDI#10
U$16: #SCK#12
U$17: #PWR#1
U$18: #SCL#18
U$19: #SDA#17
U$20: #TX#SDO#11
U$21: NEO_GPS_BOARD_SILK_FINAL#03#JPG
U$22: ##SAFE##11
U$23: L1#L28
U$24: ANT8
U$25: NEO#M9N20
U$26: ##CS##6
U$27: ##RST##12
U$28: ##RST##2
U$29: #I2C#3
U$30: #INT#10
U$31: #PPS#0
U$33: #RX#SDI#4
U$34: #SCK#3
U$35: #SCL#8
U$36: #SDA#9
U$37: #TX#SDO#5

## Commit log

2026-04-16 update kicad + document connector pinouts
2026-04-20 update rear pinout to reflect physical wiring

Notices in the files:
libs/GPS-17285/SparkFun GPS NEO_M9N_SMA/SparkFun GPS NEO_M9N_SMA.kicad_sch:
Released under the Creative Commons
https://creativecommons.org/licenses/by-sa/4.0
parts and their libraries:
Released under the Creative Commons Attribution Share-Alike 4.0 License
